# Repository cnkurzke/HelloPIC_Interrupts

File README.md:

# About

This is part of my adventure of learning how to use PIC Microcontrollers in the real world.
If you want to learn more about what a PIC is, here are plenty of online resources. E.g. see here:

* https://en.wikipedia.org/wiki/PIC_microcontrollers
* https://www.microchip.com/en-us/products/microcontrollers-and-microprocessors
* https://pic-microcontroller.com/pic16f877-based-projects-pic-microcontroller-downloadable/

My intention is to document my learning journey, so others can hopefully find it useful on
their own research and learning path. I strongly encourage everyone who finds a mistake, 
be it an oversight or something out of date, *please file a bug, or even better, contribute a fix!*

## My Setup

I try to do this as cleaply as possible, so that it can be reproduced by everyone.

My primary workstation is a standard PC with Ubuntu (currently version 20.04), and I use the 
PicKit 3. If you intend to purchase a programmer, be aware that the PicKit 2 is no longer 
supported by the current (2022) generation of development tools.

As the software environmnet, I am not happy with the Microchip tools, but it is the quickest way to
get started.
In fact, I installed a Virtual Machine, and run the MPLab IDE inside the VM. But if you have a
more "traditional" operating system, you should be fine to run this on your standard computer.
Follow the steps here:
https://www.microchip.com/en-us/tools-resources/develop/mplab-x-ide

# What Does It Do

I started with a very simple problem. For a car I'm currently restoring, I needed something
to control the "Transmission Reverse Lock-Out". For a commercial device, look at 
https://shiftsst.com/tremec-6-speed-reverse-lockout-control-module.html

What's relevant for this level of detail:

*  The goal is to drive an automotive grade 12 volt Solenoid which is wired to the car in a 
   "High-Side Switch" configuration.
   What this means:
   *  The module we build will have to be able to deliver high current, and it is an 
      "inductive load".
      Therefore I chose a beefy MOSFET to drive the signal to the transmission.
      
   *  The solenoid is permanently connected to "ground", and we have to close a switch to 12V to
      activate the solenoid and unlock the reverse gear. This means we have a 
      P-Channel MOSFET in "High Side Switching" configuration.
      For an example see here: https://www.elektormagazine.com/news/high-side-low-side-switching

    * 
      The P-Channel MOSFET needs to be driven by a 12V Gate voltage, annd can unfortunately not
      be driven by the PIC output pin. Even though the Datasheet mentions that PIC outputs are
      able to work as "open Collector" - this is only thue for voltages within the operating
      voltage level. The circeled Diode in the diagram shows that the PIC has internal 
      clamping Diodes for protection.
      
*  The logic implemented by this device is to:
  *  Whenever the vehicle is turned on: Activate the solenoid for 30 seconds 
  *  When the driver pushes a trigger buttom: Activate the solenoid for 30 seconds 

This is a fairly simple timer circuit.

# Hardware Choices

After a bit of research, I decided the 8-pin PIC 12F1572 is more than capable.
It has 6 GPIOs, and holds 2KB memory.
See the datasheet here: https://www.microchip.com/en-us/product/PIC12F1572

For the MOSFET I decided to use the: https://www.sparkfun.com/datasheets/Components/General/FQP27P06.pdf
It can easily drive 20+ Amp, and most important, it has an integrated "fly back diode" to handle switching the inductive load.

Here's an early sketch of a circuit: 

It became apparent rather quickly that the biggest challenge would be, how to drive the 12V MOSFET from the 5V PIC output.

## MOSFET Drriver

It turns out that the PIC output pins, even though they are "Open Collector" capable, they are protected by a diode, which prevents to pull-up to 12V.

I looked at various MOSFET Drivers, but they are really not needed, for the low (basically DC) switching  freqencies.
In this case, a simple NPN BJT in Open Collector mode is suficcient.

## Prototype

After a bit of breadboarding, I had the first version up and running rather quickly. 

# KiCAD Schematics

I decided to create "REAL" circuit boards. After a bit of research, the free software "KiCAD" cauught my interest. It's everything  I need, and way, way more!
See: https://www.kicad.org/

After some trial and error and watching tutorials like: https://www.youtube.com/watch?v=ia2n7P3Csac

I created this schematic:

The source for this is here: https://github.com/cnkurzke/HelloPIC_Interrupts/tree/master/schematics

# PCB Layout

With the help of KiCAD, i turned this schematic into a circuit board, and Gerber files: 
https://github.com/cnkurzke/HelloPIC_Interrupts/tree/master/schematics/KiCAD_project/PIC_Timer/gerbers

The Gerber files describe the PCB and are used to manufacture the final boards:

... stay tuned, the boards will arrive in 5 days

To be continued

# SOFTWARE 

## HelloPIC_Interrupts
Sample code for the PIC 12F1572 interrupt handling.

For a very basic introduction about Interrupts on PIC see:
https://picguides.com/beginner/interrupts.php

The Interrupt handler gets registered in main.c, with     
`IOCAF2_SetInterruptHandler(IOCAF2_CGK_InterruptHandler);`

The ISR (`IOCAF2_CGK_InterruptHandler()`) is called everytime the RA2 is pulled to LOW.

More in detail information about De-Bouncing Switches: 
http://www.ganssle.com/debouncing-pt2.htm

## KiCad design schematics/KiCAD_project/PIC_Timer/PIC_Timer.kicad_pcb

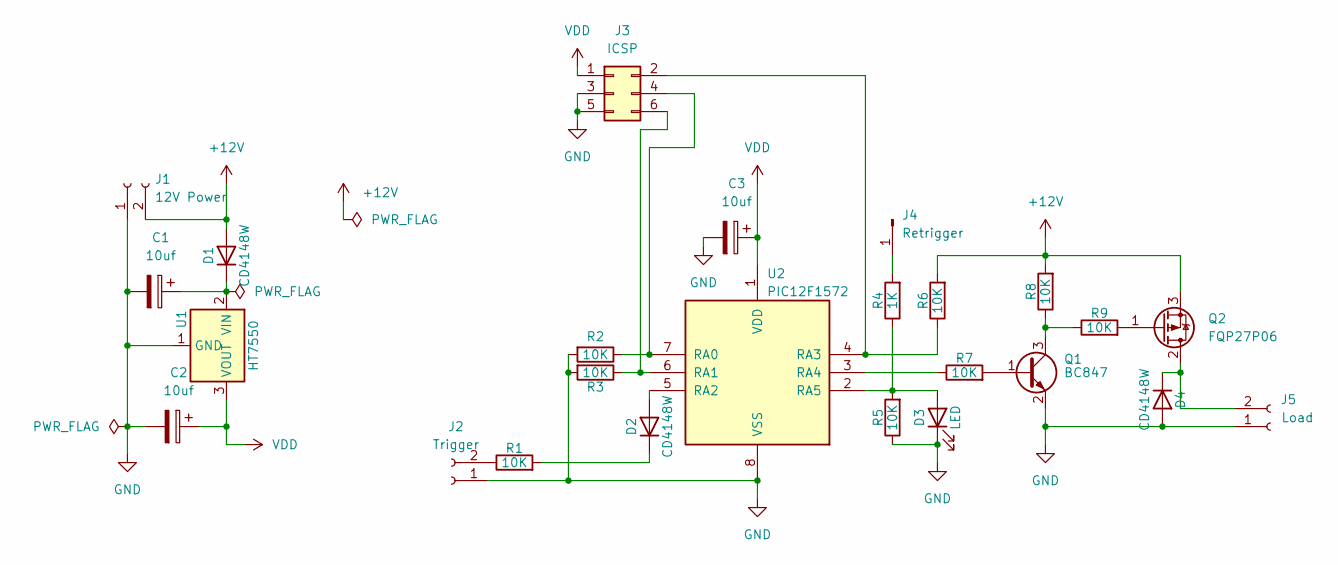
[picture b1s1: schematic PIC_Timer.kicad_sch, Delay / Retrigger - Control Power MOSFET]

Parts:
C1, C2: 10uf; CP_EIA-3216-10_Kemet-I_Pad1.58x1.35mm_HandSolder
C3: 10uf; C_1206_3216Metric_Pad1.33x1.80mm_HandSolder
D1, D2, D4: CD4148W; D_0805_2012Metric
D3: LED; LED_0805_2012Metric_Pad1.15x1.40mm_HandSolder
J1: 12V Power; JWT_A3963_1x02_P3.96mm_Vertical
J2: Trigger; JWT_A3963_1x02_P3.96mm_Vertical
J3: ICSP; PinHeader_2x03_P2.54mm_Vertical
J4: Retrigger; Pin_D0.7mm_L6.5mm_W1.8mm_FlatFork
J5: Load; JWT_A3963_1x02_P3.96mm_Vertical
Q1: BC847; SOT-23
Q2: FQP27P06; TO-220-3_Vertical
R1, R2, R3, R5, R6, R7, R8, R9: 10K; R_0805_2012Metric_Pad1.20x1.40mm_HandSolder
R4: 1K; R_0805_2012Metric_Pad1.20x1.40mm_HandSolder
U1: HT7550; SOT-89-3
U2: PIC12F1572; DIP-8_W7.62mm

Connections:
+12V: D1.2 (A), J1.2, Q2.3 (S), R6.2, R8.2
GND: C1.2, C2.2, C3.2, D3.1 (K), D4.2 (A), J1.1, J2.1, J3.3, J3.5, J5.1, Q1.2 (E), R2.2, R3.2, R5.1, U1.1 (GND), U2.8 (VSS)
unnamed: C1.1, D1.1 (K), U1.2 (VIN)
unnamed: D2.1 (K), R1.2
unnamed: D2.2 (A), U2.5 (RA2)
unnamed: D3.2 (A), R4.1, R5.2, U2.2 (RA5)
unnamed: D4.1 (K), J5.2, Q2.2 (D)
unnamed: J2.2, R1.1
unnamed: J3.2, R6.1, U2.4 (RA3)
unnamed: J3.4, R2.1, U2.7 (RA0)
unnamed: J3.6, R3.1, U2.6 (RA1)
unnamed: J4.1, R4.2
unnamed: Q1.1 (B), R7.2
unnamed: Q1.3 (C), R8.1, R9.1
unnamed: Q2.1 (G), R9.2
unnamed: R7.1, U2.3 (RA4)
VDD: C2.1, C3.1, J3.1, U1.3 (VOUT), U2.1 (VDD)

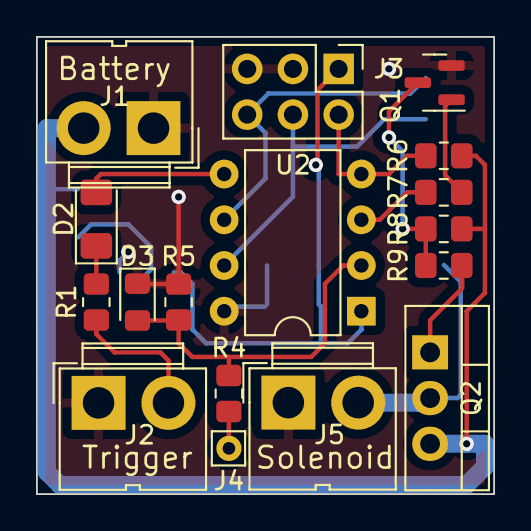
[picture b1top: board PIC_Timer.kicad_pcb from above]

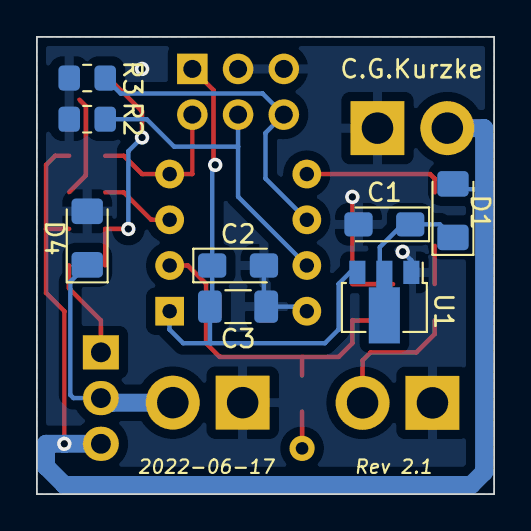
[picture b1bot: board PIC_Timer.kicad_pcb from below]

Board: 2 copper layers, 25.4 x 25.4 mm, 25 parts (8 on the bottom side), 17 nets.

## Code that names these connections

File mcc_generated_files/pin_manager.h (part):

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// get/set IO_RA0 aliases
#define IO_RA0_TRIS                 TRISAbits.TRISA0
#define IO_RA0_LAT                  LATAbits.LATA0
#define IO_RA0_PORT                 PORTAbits.RA0
#define IO_RA0_WPU                  WPUAbits.WPUA0
#define IO_RA0_OD                   ODCONAbits.ODA0
#define IO_RA0_ANS                  ANSELAbits.ANSA0
#define IO_RA0_SetHigh()            do { LATAbits.LATA0 = 1; } while(0)
#define IO_RA0_SetLow()             do { LATAbits.LATA0 = 0; } while(0)
#define IO_RA0_Toggle()             do { LATAbits.LATA0 = ~LATAbits.LATA0; } while(0)
#define IO_RA0_GetValue()           PORTAbits.RA0
#define IO_RA0_SetDigitalInput()    do { TRISAbits.TRISA0 = 1; } while(0)
#define IO_RA0_SetDigitalOutput()   do { TRISAbits.TRISA0 = 0; } while(0)
#define IO_RA0_SetPullup()          do { WPUAbits.WPUA0 = 1; } while(0)
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// get/set IO_RA1 aliases
#define IO_RA1_TRIS                 TRISAbits.TRISA1
#define IO_RA1_LAT                  LATAbits.LATA1
#define IO_RA1_PORT                 PORTAbits.RA1
#define IO_RA1_WPU                  WPUAbits.WPUA1
#define IO_RA1_OD                   ODCONAbits.ODA1
#define IO_RA1_ANS                  ANSELAbits.ANSA1
#define IO_RA1_SetHigh()            do { LATAbits.LATA1 = 1; } while(0)
#define IO_RA1_SetLow()             do { LATAbits.LATA1 = 0; } while(0)
#define IO_RA1_Toggle()             do { LATAbits.LATA1 = ~LATAbits.LATA1; } while(0)
#define IO_RA1_GetValue()           PORTAbits.RA1
#define IO_RA1_SetDigitalInput()    do { TRISAbits.TRISA1 = 1; } while(0)
#define IO_RA1_SetDigitalOutput()   do { TRISAbits.TRISA1 = 0; } while(0)
#define IO_RA1_SetPullup()          do { WPUAbits.WPUA1 = 1; } while(0)
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// get/set IO_RA2 aliases
#define IO_RA2_TRIS                 TRISAbits.TRISA2
#define IO_RA2_LAT                  LATAbits.LATA2
#define IO_RA2_PORT                 PORTAbits.RA2
#define IO_RA2_WPU                  WPUAbits.WPUA2
#define IO_RA2_OD                   ODCONAbits.ODA2
#define IO_RA2_ANS                  ANSELAbits.ANSA2
#define IO_RA2_SetHigh()            do { LATAbits.LATA2 = 1; } while(0)
#define IO_RA2_SetLow()             do { LATAbits.LATA2 = 0; } while(0)
#define IO_RA2_Toggle()             do { LATAbits.LATA2 = ~LATAbits.LATA2; } while(0)
#define IO_RA2_GetValue()           PORTAbits.RA2
#define IO_RA2_SetDigitalInput()    do { TRISAbits.TRISA2 = 1; } while(0)
#define IO_RA2_SetDigitalOutput()   do { TRISAbits.TRISA2 = 0; } while(0)
#define IO_RA2_SetPullup()          do { WPUAbits.WPUA2 = 1; } while(0)
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// get/set IO_RA4 aliases
#define IO_RA4_TRIS                 TRISAbits.TRISA4
#define IO_RA4_LAT                  LATAbits.LATA4
#define IO_RA4_PORT                 PORTAbits.RA4
#define IO_RA4_WPU                  WPUAbits.WPUA4
#define IO_RA4_OD                   ODCONAbits.ODA4
#define IO_RA4_ANS                  ANSELAbits.ANSA4
#define IO_RA4_SetHigh()            do { LATAbits.LATA4 = 1; } while(0)
#define IO_RA4_SetLow()             do { LATAbits.LATA4 = 0; } while(0)
#define IO_RA4_Toggle()             do { LATAbits.LATA4 = ~LATAbits.LATA4; } while(0)
#define IO_RA4_GetValue()           PORTAbits.RA4
#define IO_RA4_SetDigitalInput()    do { TRISAbits.TRISA4 = 1; } while(0)
#define IO_RA4_SetDigitalOutput()   do { TRISAbits.TRISA4 = 0; } while(0)
#define IO_RA4_SetPullup()          do { WPUAbits.WPUA4 = 1; } while(0)
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// get/set IO_RA5 aliases
#define IO_RA5_TRIS                 TRISAbits.TRISA5
#define IO_RA5_LAT                  LATAbits.LATA5
#define IO_RA5_PORT                 PORTAbits.RA5
#define IO_RA5_WPU                  WPUAbits.WPUA5
#define IO_RA5_OD                   ODCONAbits.ODA5
#define IO_RA5_SetHigh()            do { LATAbits.LATA5 = 1; } while(0)
#define IO_RA5_SetLow()             do { LATAbits.LATA5 = 0; } while(0)
#define IO_RA5_Toggle()             do { LATAbits.LATA5 = ~LATAbits.LATA5; } while(0)
#define IO_RA5_GetValue()           PORTAbits.RA5
#define IO_RA5_SetDigitalInput()    do { TRISAbits.TRISA5 = 1; } while(0)
#define IO_RA5_SetDigitalOutput()   do { TRISAbits.TRISA5 = 0; } while(0)
#define IO_RA5_SetPullup()          do { WPUAbits.WPUA5 = 1; } while(0)
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
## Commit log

2022-03-28 initial version
2022-03-29 Create LICENSE
2022-04-03 Reversed the output RA4 to accommodate open-collector transistor driver for MOSFET
2022-04-03 Added KiKAD Schematics files
2022-04-11 Created KiCAD schematics
2022-04-13 placed and rendered in 1 sqare inch
2022-04-16 Rev 1.0 Gerber Files
2022-04-22 Files as sent to PCB maker
2022-04-22 Photos added
2022-04-23 Documentation
2022-04-29 clean up, deleted stale PDFs & Gerbers
2022-05-26 added open collector png
2022-05-26 minor fixes
2022-05-27 converted to SMD
2022-05-30 Rev 2.0 of SMD PCB
2022-05-30 update BOM, PDFs
2022-06-02 added BOM and updated Schmatics PDF
2022-06-03 Delete PIC_Timer.pdf
    moved to one level up
2022-06-03 Configured RA0 and RA1 as INPUT, hardwired to GND to improve ESD resistance
2022-06-03 RA0 and RA1 set as inputs to improve ESD
2022-06-17 changed Diodes from 0805 to 1206 to accomodate the 1n4148 SMD

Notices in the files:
mcc_generated_files/pin_manager.h:
(c) 2018 Microchip Technology Inc. and its subsidiaries.
